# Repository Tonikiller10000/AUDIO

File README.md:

# AUDIO
Some audio related projects(amps, pedals, midi, etc.).

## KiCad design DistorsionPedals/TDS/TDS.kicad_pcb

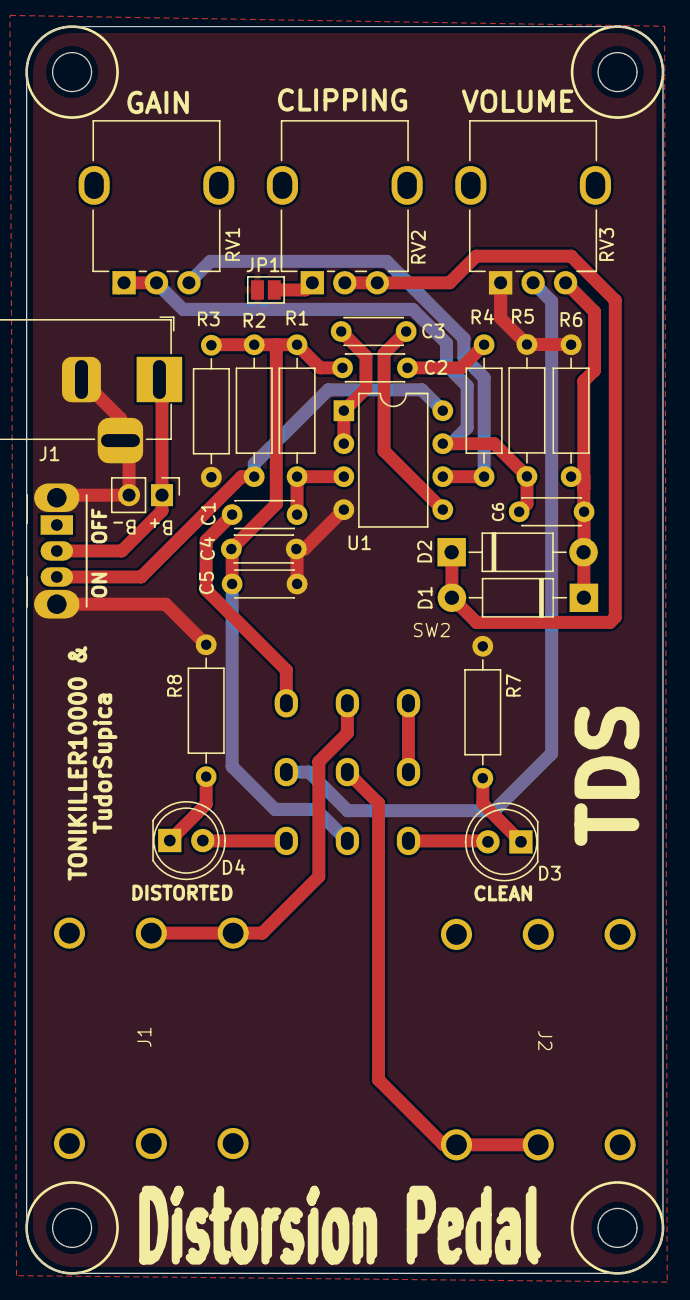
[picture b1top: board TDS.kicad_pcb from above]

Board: 2 copper layers, 49.0 x 96.0 mm, 29 parts (0 on the bottom side), 22 nets.

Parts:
C1, C2, C3, C4, C6: 10uF; C_Disc_D4.3mm_W1.9mm_P5.00mm
C5: 100nF; C_Disc_D4.3mm_W1.9mm_P5.00mm
D1, D2: D; D_DO-41_SOD81_P10.16mm_Horizontal
D3: GREEN; LED_D5.0mm
D4: RED; LED_D5.0mm
J1: Barrel_Jack; BarrelJack_Horizontal
J1#2: Barrel_Jack; PJ-664C
J2: BATT; PinHeader_1x02_P2.54mm_Vertical
J2#2: BATT; PJ-664C
JP1: Jumper_2_Open; SolderJumper-2_P1.3mm_Open_Pad1.0x1.5mm
R1: 100k; R_Axial_DIN0207_L6.3mm_D2.5mm_P10.16mm_Horizontal
R2, R3, R6: 10K; R_Axial_DIN0207_L6.3mm_D2.5mm_P10.16mm_Horizontal
R4, R7, R8: 1K; R_Axial_DIN0207_L6.3mm_D2.5mm_P10.16mm_Horizontal
R5: 3.8K; R_Axial_DIN0207_L6.3mm_D2.5mm_P10.16mm_Horizontal
RV1, RV3: 100K; Potentiometer_Alpha_RD901F-40-00D_Single_Vertical
RV2: 10K; Potentiometer_Alpha_RD901F-40-00D_Single_Vertical
SW1: POW; SW_CuK_OS102011MA1QN1_SPDT_Angled
SW2: FootSwitch
U1: TL072; DIP-8_W7.62mm

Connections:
CLEAN: C1.1, SW2.1 (C)
DISTORTED: RV3.2, SW2.4 (C)
GND: C4.1, C5.1, J1.2, J1.3, J2.2, JP1.2 (B), R3.1, R5.1, R6.1, R7.1, R8.1, RV3.1, U1.4 (V-)
INPUT: J1#2.L, J1#2.R, SW2.2 (B)
unnamed: C2.2, R4.2
unnamed: C6.2, R5.2, RV1.1, RV1.2, U1.7
unnamed: D1.2 (A), D2.1 (K), RV2.2, RV2.3
unnamed: C6.1, D1.1 (K), D2.2 (A), R6.2, RV3.3
unnamed: D3.2 (A), SW2.9 (A)
unnamed: D3.1 (K), R7.2
unnamed: D4.2 (A), SW2.7 (C)
unnamed: D4.1 (K), R8.2
unnamed: JP1.1 (A), RV2.1
unnamed: SW2.3 (A), SW2.6 (A)
unnamed: C1.2, R1.1, U1.3 (+)
unnamed: C3.2, U1.1, U1.2 (-)
unnamed: C3.1, U1.5 (+)
unnamed: R4.1, RV1.3, U1.6 (-)
OUTPUT: J2#2.L, J2#2.R, SW2.5 (B)
POW: J1.1, J2.1, SW1.2 (B)
VCC: R2.2, SW1.3 (A), U1.8 (V+)
VDD: C2.1, C4.2, C5.2, R1.2, R2.1, R3.2, SW2.8 (B)

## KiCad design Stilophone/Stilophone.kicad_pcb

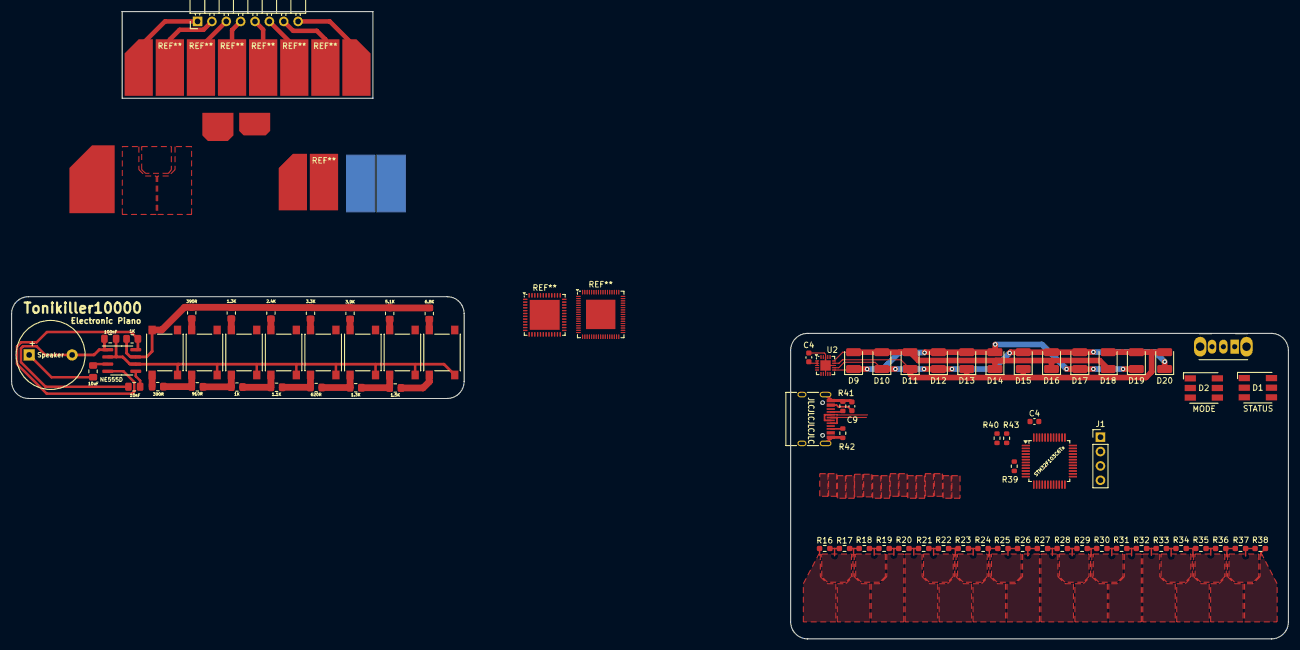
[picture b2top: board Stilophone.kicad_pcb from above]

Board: 2 copper layers, 225.7 x 110.9 mm, 78 parts (0 on the bottom side), 53 nets.

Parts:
C1: 10nF; C_0805_2012Metric_Pad1.18x1.45mm_HandSolder
C2: 100nF; C_0805_2012Metric_Pad1.18x1.45mm_HandSolder
C3: 10uF; C_0805_2012Metric_Pad1.18x1.45mm_HandSolder
C4, C4#2, C9: 10uF; C_0603_1608Metric
D1: STATUS; LED_RGB_5050-6
D2: MODE; LED_RGB_5050-6
D9, D10, D11, D12, D13, D14, D15, D16, D17, D18, D19, D20: D; LED_1210_3225Metric_Pad1.42x2.65mm_HandSolder
J1: STLINK; PinHeader_1x04_P2.54mm_Vertical
J2: USB_C_USB2.0; USB_C_Receptacle_HRO_TYPE-C-31-M-12
LS1: Speaker; Buzzer_12x9.5RM7.6
R1, R6: 1K; R_0805_2012Metric_Pad1.20x1.40mm_HandSolder
R2, R3: 390R; R_0805_2012Metric_Pad1.20x1.40mm_HandSolder
R4: 910R; R_0805_2012Metric_Pad1.20x1.40mm_HandSolder
R5, R12: 1.3K; R_0805_2012Metric_Pad1.20x1.40mm_HandSolder
R7: 2.4K; R_0805_2012Metric_Pad1.20x1.40mm_HandSolder
R8: 1.1K; R_0805_2012Metric_Pad1.20x1.40mm_HandSolder
R9: 3.3K; R_0805_2012Metric_Pad1.20x1.40mm_HandSolder
R10: 620R; R_0805_2012Metric_Pad1.20x1.40mm_HandSolder
R11: 3.9K; R_0805_2012Metric_Pad1.20x1.40mm_HandSolder
R13: 5.1K; R_0805_2012Metric_Pad1.20x1.40mm_HandSolder
R14: 1.5K; R_0805_2012Metric_Pad1.20x1.40mm_HandSolder
R15: 6.8K; R_0805_2012Metric_Pad1.20x1.40mm_HandSolder
R16, R17, R18, R19, R20, R21, R22, R23, R24, R25, R26, R27, R28, R29, R30, R31, R32, R33, R34, R35, R36, R37, R38: R; R_0603_1608Metric_Pad0.98x0.95mm_HandSolder
R39, R40, R43: 10K; R_0603_1608Metric
R41, R42: 5K1; R_0603_1608Metric
SW1: SW_Push; SW_CuK_OS102011MA1QN1_SPDT_Angled
SW1#2, SW2, SW3, SW4, SW5, SW6, SW7, SW8: SW_Push; SW_Push_1P1T_NO_6x6mm_H9.5mm
U1: NE555D; SOIC-8_3.9x4.9mm_P1.27mm
U2: UQFN-20-1EP_3x3mm_P0.4mm_EP1.85x1.85mm
U3: STM32F103C6Tx; LQFP-48_7x7mm_P0.5mm

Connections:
+3.3V: J1.1, R39.2, R40.2, R43.2, U3.1 (VBAT), U3.9 (VDDA), U3.24 (VDD), U3.36 (VDD), U3.48 (VDD)
+5V: C4.1, C4#2.1, U2.1 (VIN), U2.2 (VIN), U2.3 (VCC)
Earth: C1.1, C2.2, LS1.2, U1.1 (GND)
GND: C4.2, C4#2.2, C9.2, J1.4, R16.2, R41.2, R42.2, U2.8 (GND), U2.13 (GND), U2.18 (GND), U2.21 (GND), U3.8 (VSSA), U3.23 (VSS), U3.35 (VSS), U3.47 (VSS)
LED3A: D11.1 (K), D13.1 (K), D15.1 (K), D18.2 (A), D19.2 (A), D20.2 (A), U2.14 (LEDB3)
LED4A: D9.2 (A), D10.2 (A), D11.2 (A), D14.1 (K), D16.1 (K), D18.1 (K), U2.15 (LEDB4)
LEDA1: D9.1 (K), D12.2 (A), D13.2 (A), D14.2 (A), D17.1 (K), D19.1 (K), U2.11 (LEDB1)
LEDA2: D10.1 (K), D12.1 (K), D15.2 (A), D16.2 (A), D17.2 (A), D20.1 (K), U2.12 (LEDB2)
NOTE: R38.1, U3.10 (PA0)
unnamed: C3.2, LS1.1
unnamed: D1.1 (BA), D1.2 (RA), D1.3 (GA), D2.4 (GK), U2.6 (LEDA1)
unnamed: D1.6 (BK), D2.1 (BA), D2.2 (RA), D2.3 (GA), U2.7 (LEDA2)
unnamed: D1.4 (GK), D2.5 (RK), U2.10 (LED4A)
unnamed: D1.5 (RK), D2.6 (BK), U2.9 (LED3A)
unnamed: R2.1, R3.1, R4.2, SW2.1
unnamed: R4.1, R5.1, R6.2, SW3.1
unnamed: R6.1, R7.1, R8.2, SW4.1
unnamed: R10.1, R11.1, R12.2, SW6.1
unnamed: R8.1, R9.1, R10.2, SW5.1
unnamed: R12.1, R13.1, R14.2, SW7.1
unnamed: R14.1, R15.1, SW8.1
unnamed: R16.1, R17.1
unnamed: R17.2, R18.2
unnamed: R18.1, R19.2
unnamed: R19.1, R20.2
unnamed: R20.1, R21.1
unnamed: R21.2, R22.2
unnamed: R22.1, R23.2
unnamed: R23.1, R24.2
unnamed: R24.1, R25.1
unnamed: R25.2, R26.2
unnamed: R26.1, R27.2
unnamed: R27.1, R28.2
unnamed: R28.1, R29.1
unnamed: R29.2, R30.2
unnamed: R30.1, R31.2
unnamed: R31.1, R32.2
unnamed: R32.1, R33.1
unnamed: R33.2, R34.2
unnamed: R34.1, R35.2
unnamed: R35.1, R36.2
unnamed: R36.1, R37.1
unnamed: R37.2, R38.2
unnamed: C1.2, U1.5 (CV)
unnamed: R1.2, R2.2, R3.2, R5.2, R7.2, R9.2, R11.2, R13.2, R15.2, SW1.1, SW1#2.1, U1.7 (DIS)
unnamed: C3.1, U1.3 (Q)
unnamed: C2.1, SW1.2, SW1#2.2, SW2.2, SW3.2, SW4.2, SW5.2, SW6.2, SW7.2, SW8.2, U1.2 (TR), U1.6 (THR)
unnamed: R39.1, U3.7 (NRST)
SCL: R40.1, U2.4 (SCL)
SDA: R43.1, U2.5 (SDA)
SWCLK: J1.3, U3.37 (SYS_JTCK-SWCLK)
SWDIO: J1.2, U3.34 (SYS_JTMS-SWDIO)
VCC: R1.1, U1.4 (R), U1.8 (VCC)

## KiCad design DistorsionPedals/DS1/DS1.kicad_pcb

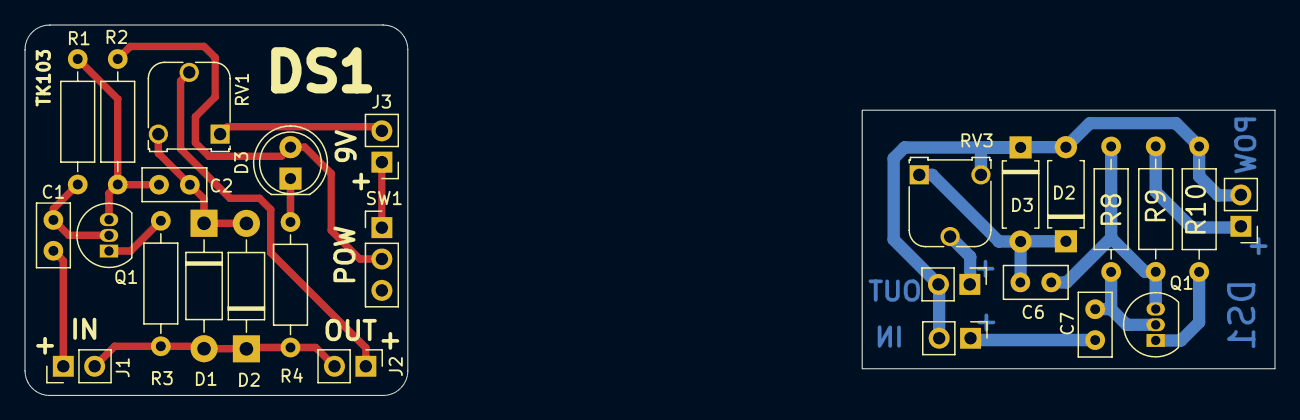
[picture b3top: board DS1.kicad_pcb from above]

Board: 2 copper layers, 101.2 x 30.0 mm, 24 parts (0 on the bottom side), 10 nets.

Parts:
C1, C2, C6, C7: 100nF; C_Disc_D5.0mm_W2.5mm_P2.50mm
D1, D2#2: D; D_DO-41_SOD81_P10.16mm_Horizontal
D2, D3: D; D_A-405_P7.62mm_Horizontal
D3#2: RED; LED_D5.0mm
J1, J2: Conn_01x02; PinHeader_1x02_P2.54mm_Vertical
J3: 9V_BATT; PinHeader_1x02_P2.54mm_Vertical
Q1, Q1#2: 2N3904; TO-92_Inline
R1, R8: 2.2M; R_Axial_DIN0207_L6.3mm_D2.5mm_P10.16mm_Horizontal
R2, R9: 47K; R_Axial_DIN0207_L6.3mm_D2.5mm_P10.16mm_Horizontal
R3, R10: 680R; R_Axial_DIN0207_L6.3mm_D2.5mm_P10.16mm_Horizontal
R4: 10K; R_Axial_DIN0207_L6.3mm_D2.5mm_P10.16mm_Horizontal
RV1, RV3: 100K; Potentiometer_Runtron_RM-065_Vertical
SW1: ENABLE; PinHeader_1x03_P2.54mm_Vertical

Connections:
+9V: D3#2.2 (A), R2.2, R9.2, SW1.2 (B)
GND: D1.2 (A), D2.2 (A), D2#2.1 (K), D3.1 (K), J1.2, J2.2, J3.2, R3.1, R4.1, R10.1, RV1.1, RV3.3
IN: C1.1, C7.1, J1.1
unnamed: C2.2, D1.1 (K), D2#2.2 (A), RV1.3
unnamed: D3#2.1 (K), R4.2
unnamed: J3.1, SW1.1 (C)
unnamed: C1.2, C7.2, Q1.2 (B), Q1#2.2 (B), R1.1, R8.1
unnamed: C2.1, C6.1, Q1.3 (C), Q1#2.3 (C), R1.2, R2.1, R8.2, R9.1
unnamed: Q1.1 (E), Q1#2.1 (E), R3.2, R10.2
OUT: J2.1, RV1.2, RV3.2

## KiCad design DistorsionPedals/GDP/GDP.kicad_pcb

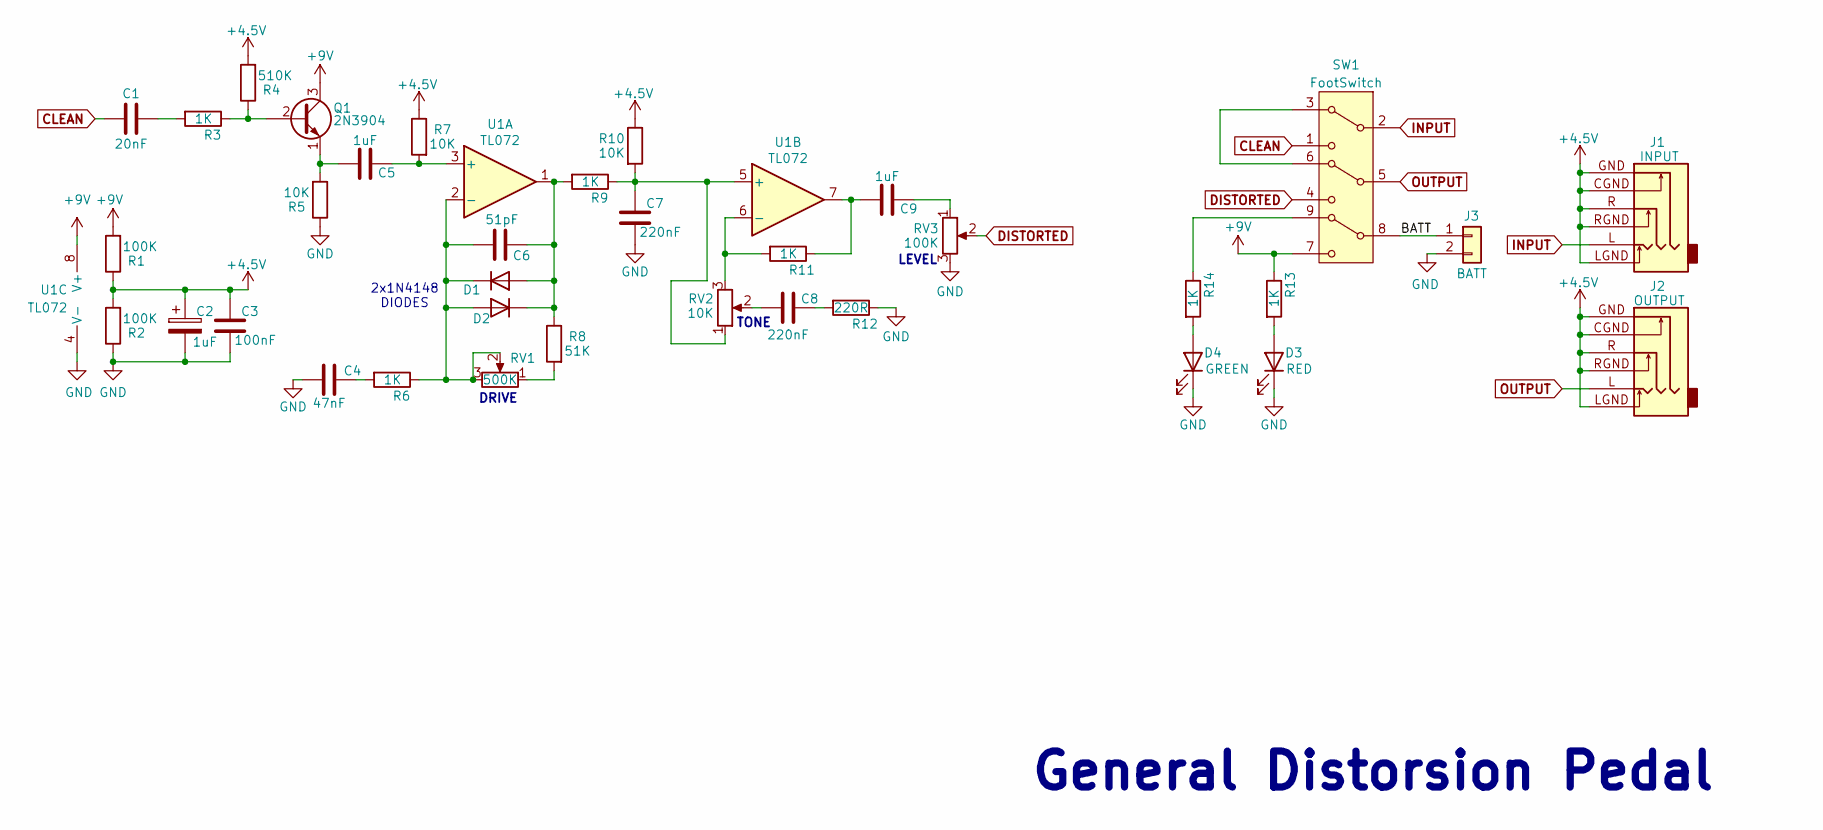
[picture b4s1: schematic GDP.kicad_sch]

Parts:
C1: 20nF; C_Disc_D4.3mm_W1.9mm_P5.00mm
C2: 1uF
C3: 100nF; C_Disc_D4.3mm_W1.9mm_P5.00mm
C4: 47nF; C_Disc_D4.3mm_W1.9mm_P5.00mm
C5, C9: 1uF; C_Disc_D4.3mm_W1.9mm_P5.00mm
C6: 51pF; C_Disc_D4.3mm_W1.9mm_P5.00mm
C7, C8: 220nF; C_Disc_D4.3mm_W1.9mm_P5.00mm
D1, D2: D; D_DO-41_SOD81_P10.16mm_Horizontal
D3: RED; LED_D5.0mm
D4: GREEN; LED_D5.0mm
J1: INPUT
J2: OUTPUT
J3: BATT
Q1: 2N3904; TO-92_Inline
R1, R2: 100K; R_Axial_DIN0207_L6.3mm_D2.5mm_P10.16mm_Horizontal
R3, R6, R9, R11, R13, R14: 1K; R_Axial_DIN0207_L6.3mm_D2.5mm_P10.16mm_Horizontal
R4: 510K; R_Axial_DIN0207_L6.3mm_D2.5mm_P10.16mm_Horizontal
R5, R7, R10: 10K; R_Axial_DIN0207_L6.3mm_D2.5mm_P10.16mm_Horizontal
R8: 51K; R_Axial_DIN0207_L6.3mm_D2.5mm_P10.16mm_Horizontal
R12: 220R; R_Axial_DIN0207_L6.3mm_D2.5mm_P10.16mm_Horizontal
RV1: 500K
RV2: 10K
RV3: 100K
SW1: FootSwitch; Nidec_Copal_CAS-120A
U1: TL072; DIP-8_W7.62mm

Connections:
+4.5V: C2.1, C3.2, J1.CGND, J1.GND, J1.LGND, J1.R, J1.RGND, J2.CGND, J2.GND, J2.LGND, J2.R, J2.RGND, R1.1, R2.2, R4.2, R7.1, R10.1
+9V: Q1.3 (C), R1.2, R13.1, SW1.7 (C), U1.8 (V+)
/BATT: J3.1, SW1.8 (B)
CLEAN: C1.1, SW1.1 (C)
DISTORTED: RV3.2, SW1.4 (C)
GND: C2.2, C3.1, C4.2, C7.1, D3.1 (K), D4.1 (K), J3.2, R2.1, R5.1, R12.1, RV3.3, U1.4 (V-)
INPUT: J1.L, SW1.2 (B)
unnamed: C1.2, R3.2
unnamed: C4.1, R6.2
unnamed: C8.1, R12.2
unnamed: C8.2, RV2.2
unnamed: C9.1, RV3.1
unnamed: C9.2, R11.1, U1.7
unnamed: C6.2, D1.2 (A), D2.1 (K), R8.1, R9.2, U1.1
unnamed: C6.1, D1.1 (K), D2.2 (A), R6.1, RV1.2, RV1.3, U1.2 (-)
unnamed: D3.2 (A), R13.2
unnamed: D4.2 (A), R14.2
unnamed: Q1.2 (B), R3.1, R4.1
unnamed: C5.2, Q1.1 (E), R5.2
unnamed: R8.2, RV1.1
unnamed: R14.1, SW1.9 (A)
unnamed: SW1.3 (A), SW1.6 (A)
unnamed: C5.1, R7.2, U1.3 (+)
unnamed: C7.2, R9.1, R10.2, RV2.1, U1.5 (+)
unnamed: R11.2, RV2.3, U1.6 (-)
OUTPUT: J2.L, SW1.5 (B)

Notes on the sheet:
General Distorsion Pedal
LEVEL
TONE
2x1N4148 DIODES
DRIVE

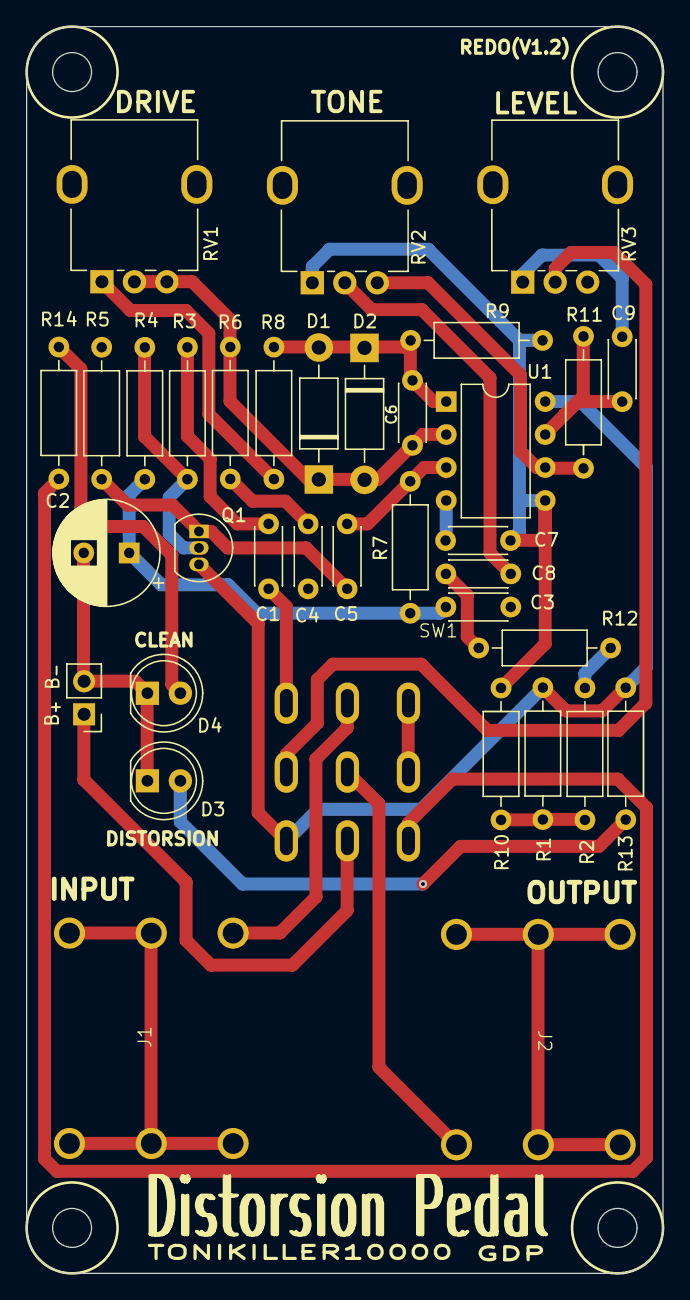
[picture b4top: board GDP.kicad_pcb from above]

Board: 2 copper layers, 49.0 x 96.0 mm, 36 parts (0 on the bottom side), 26 nets.

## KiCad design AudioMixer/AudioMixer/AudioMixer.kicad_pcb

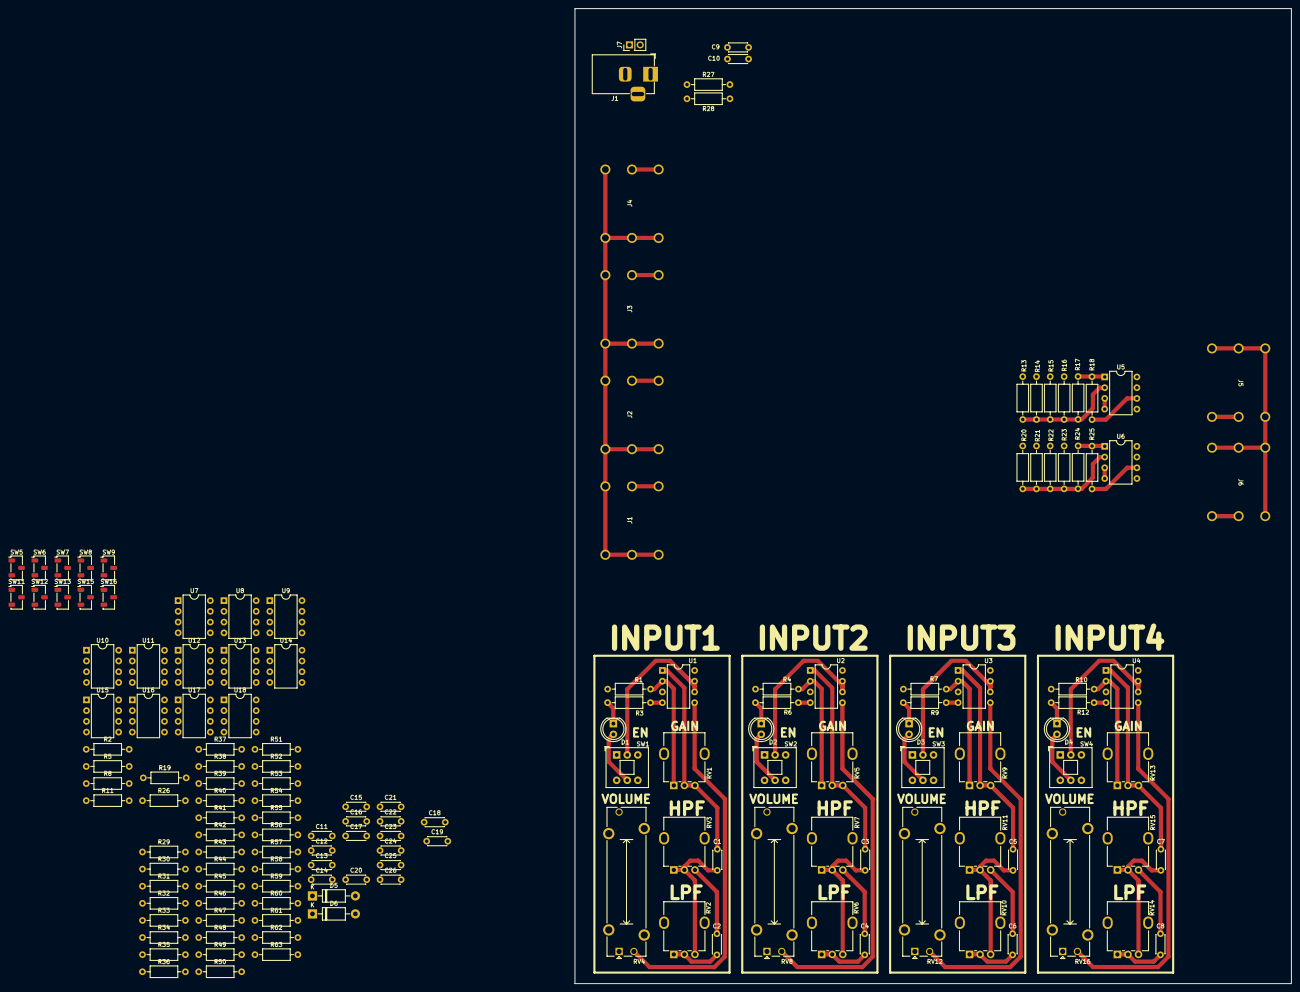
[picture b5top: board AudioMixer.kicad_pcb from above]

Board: 2 copper layers, 169.6 x 230.8 mm, 151 parts (0 on the bottom side), 94 nets.

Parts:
C1, C2, C3, C4, C5, C6, C7, C8, C11, C18, C21, C22, C23, C24, C25, C26: 10uF; C_Disc_D4.3mm_W1.9mm_P5.00mm
C9, C10, C14, C15, C19: 100nF; C_Disc_D4.3mm_W1.9mm_P5.00mm
C12, C13, C16, C17: 10nF; C_Disc_D4.3mm_W1.9mm_P5.00mm
C20: C; C_Disc_D4.3mm_W1.9mm_P5.00mm
D1, D2, D3, D4: RED; LED_D5.0mm
D5, D6: D; D_DO-41_SOD81_P10.16mm_Horizontal
J1, J2, J3, J4: INPUT; PJ-664C
J1#2: Barrel_Jack; BarrelJack_Horizontal
J5, J6: OUTPUT; PJ-664C
J7: PinHeader_1x02_P2.54mm_Vertical
R1, R4, R7, R10, R18, R19, R25, R26, R41, R45, R53, R58, R59, R61, R62: 1K; R_Axial_DIN0207_L6.3mm_D2.5mm_P10.16mm_Horizontal
R2, R3, R5, R6, R8, R9, R11, R12, R30, R31, R34, R37, R38, R39, R40, R42: 10K; R_Axial_DIN0207_L6.3mm_D2.5mm_P10.16mm_Horizontal
R13, R14, R15, R16, R17, R20, R21, R22, R23, R24, R28, R29, R32, R33, R46, R47, R48, R49, R50, R51, R52, R54, R55, R56, R57, R60, R63: 100K; R_Axial_DIN0207_L6.3mm_D2.5mm_P10.16mm_Horizontal
R27: 47K; R_Axial_DIN0207_L6.3mm_D2.5mm_P10.16mm_Horizontal
R35: 33K; R_Axial_DIN0207_L6.3mm_D2.5mm_P10.16mm_Horizontal
R36: 68K; R_Axial_DIN0207_L6.3mm_D2.5mm_P10.16mm_Horizontal
R43, R44: R; R_Axial_DIN0207_L6.3mm_D2.5mm_P10.16mm_Horizontal
RV1, RV2, RV3, RV5, RV6, RV7, RV9, RV10, RV11, RV13, RV14, RV15: 100K; Potentiometer_Alpha_RD901F-40-00D_Single_Vertical
RV4, RV8, RV12, RV16: 100K; Potentiometer_Bourns_PTA2043_Single_Slide
SW1, SW2, SW3, SW4: EN; SW_Push_2P2T_Toggle_CK_PVA2xxH3xxxxxxV2
SW5, SW6: EN; Nidec_Copal_CAS-120A
SW7: POW; Nidec_Copal_CAS-120A
SW8, SW9, SW11, SW12, SW13, SW15, SW16: CH1; Nidec_Copal_CAS-120A
U1, U2, U3, U4, U5, U6, U7, U8, U9, U10, U11, U12, U13, U14, U16, U17, U18: TL072; DIP-8_W7.62mm
U15: NE555P; DIP-8_W7.62mm

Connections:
3V: R32.1, R33.1
+4.5V: U9.6 (-), U10.5 (+)
/INPUT1: J1.L, J1.R, R2.2, U1.3 (+)
/INPUT2: J2.L, J2.R, R5.2, U2.3 (+)
/INPUT3: J3.L, J3.R, R8.2, U3.3 (+)
/INPUT4: J4.L, J4.R, R11.2, U4.3 (+)
CH1_to_OUT1: R13.2, R20.2, SW12.1 (C)
CH2_to_OUT1: R14.2, R21.2
CH3_to_OUT1: R15.2, R22.2
CH4_to_OUT1: R16.2, R23.2
GND: C2.2, C4.2, C6.2, C8.2, C11.1, C15.1, C16.1, C17.1, C18.1, C19.1, C20.1, C22.2, C24.2, C26.2, R1.2, R3.1, R4.2, R6.1, R7.2, R9.1, R10.2, R12.1, R34.1, R35.2, R41.1, R42.1, R45.2, R53.2, R62.2, RV3.3, RV4.1, RV7.3, RV8.1, RV11.3, RV12.1, RV15.3, RV16.1, U1.4 (V-), U2.4 (V-), U3.4 (V-), U4.4 (V-), U5.3 (+), U5.4 (V-), U5.5 (+), U6.3 (+), U6.4 (V-), U6.5 (+), U7.5 (+), U8.5 (+), U11.4 (V-), U12.5 (+), U15.1 (GND), U16.5 (+), U17.5 (+), U18.5 (+)
unnamed: C1.1, RV2.3, RV3.1, RV3.2
unnamed: C1.2, RV1.2, RV1.3, U1.1
unnamed: C2.1, RV2.1, RV2.2, RV4.3
unnamed: C3.1, RV6.3, RV7.1, RV7.2
unnamed: C3.2, RV5.2, RV5.3, U2.1
unnamed: C4.1, RV6.1, RV6.2, RV8.3
unnamed: C5.1, RV10.3, RV11.1, RV11.2
unnamed: C5.2, RV9.2, RV9.3, U3.1
unnamed: C6.1, RV10.1, RV10.2, RV12.3
unnamed: C7.1, RV14.3, RV15.1, RV15.2
unnamed: C7.2, RV13.2, RV13.3, U4.1
unnamed: C8.1, RV14.1, RV14.2, RV16.3
unnamed: C9.1, R27.2, U10.7
unnamed: C10.1, R29.1, U12.7
unnamed: C12.1, C13.2, C16.2, C17.2
unnamed: C12.2, R37.2, R39.1, U14.7
unnamed: C21.2, C23.2, C25.2, R59.1
unnamed: D1.2 (A), SW1.5 (B)
unnamed: D1.1 (K), R3.2
unnamed: D2.2 (A), SW2.5 (B)
unnamed: D2.1 (K), R6.2
unnamed: D3.2 (A), SW3.5 (B)
unnamed: D3.1 (K), R9.2
unnamed: D4.2 (A), SW4.5 (B)
unnamed: D4.1 (K), R12.2
unnamed: D5.2 (A), D6.1 (K)
unnamed: D5.1 (K), D6.2 (A), SW15.3 (A), SW16.3 (A)
unnamed: R17.1, R18.2, U5.1
unnamed: R24.1, R25.2, U6.1, U7.7
unnamed: R28.1, U9.7
unnamed: R30.2, R31.2, U11.7
unnamed: R36.1, U13.7
unnamed: R37.1, R38.2
unnamed: R46.2, U16.1
unnamed: R56.2, U11.1
unnamed: R57.1, R58.2, U17.7
unnamed: R60.1, R61.2, U18.7
unnamed: R63.2, U17.1
unnamed: U6.7, U8.7
unnamed: SW1.2 (B), U1.6 (-), U1.7
unnamed: SW2.2 (B), U2.6 (-), U2.7
unnamed: SW3.2 (B), U3.6 (-), U3.7
unnamed: SW4.2 (B), U4.6 (-), U4.7
unnamed: R19.1, SW5.2 (B)
unnamed: R26.1, SW6.2 (B)
unnamed: SW8.2 (B), SW9.2 (B), SW11.2 (B), SW12.2 (B), SW13.2 (B)
unnamed: SW15.1 (C), SW16.1 (C)
unnamed: R1.1, RV1.1, U1.2 (-)
unnamed: RV4.2, U1.5 (+)
unnamed: R4.1, RV5.1, U2.2 (-)
unnamed: RV8.2, U2.5 (+)
unnamed: R7.1, RV9.1, U3.2 (-)
unnamed: RV12.2, U3.5 (+)
unnamed: R10.1, RV13.1, U4.2 (-)
unnamed: RV16.2, U4.5 (+)
unnamed: R13.1, R14.1, R15.1, R16.1, R17.2, U5.2 (-)
unnamed: R18.1, U5.6 (-)
unnamed: R20.1, R21.1, R22.1, R23.1, R24.2, U6.2 (-)
unnamed: R25.1, U6.6 (-)
unnamed: R27.1, R28.2, U9.5 (+)
unnamed: C9.2, U10.6 (-)
unnamed: C24.1, U11.3 (+)
unnamed: R53.1, U11.2 (-)
unnamed: R31.1, R34.2, U11.5 (+)
unnamed: C11.2, U11.6 (-)
unnamed: C10.2, R29.2, R30.1, U12.6 (-)
unnamed: C14.2, C15.2, U13.5 (+)
unnamed: R35.1, R36.2, U13.6 (-)
unnamed: R39.2, R41.2, U14.5 (+)
unnamed: C13.1, R38.1, U14.6 (-)
unnamed: R43.1, R44.2, U15.7 (DIS)
unnamed: C20.2, R44.1, U15.2 (TR), U15.6 (THR)
unnamed: C22.1, U16.3 (+)
unnamed: R45.1, U16.2 (-)
unnamed: R58.1, U16.6 (-)
unnamed: C26.1, U17.3 (+)
unnamed: R62.1, U17.2 (-)
unnamed: R57.2, U17.6 (-)
unnamed: R60.2, U18.6 (-)
OUTPUT1: J5.L, J5.R, SW5.3 (A), SW6.3 (A)
OUTPUT2: J6.L, J6.R
VCC: C18.2, C19.2, R40.1, R42.2, R43.2, U15.4 (R), U15.8 (VCC)
VDD: J1.CGND, J1.GND, J1.LGND, J1.RGND, J2.CGND, J2.GND, J2.LGND, J2.RGND, J3.CGND, J3.GND, J3.LGND, J3.RGND, J4.CGND, J4.GND, J4.LGND, J4.RGND, J5.CGND, J5.GND, J5.LGND, J5.RGND, J6.CGND, J6.GND, J6.LGND, J6.RGND, R2.1, R5.1, R8.1, R11.1, R40.2, SW1.6 (C), SW2.4 (A), SW3.4 (A), SW4.4 (A), SW7.3 (A), U1.8 (V+), U2.8 (V+), U3.8 (V+), U4.8 (V+), U5.8 (V+), U6.8 (V+), U11.8 (V+)

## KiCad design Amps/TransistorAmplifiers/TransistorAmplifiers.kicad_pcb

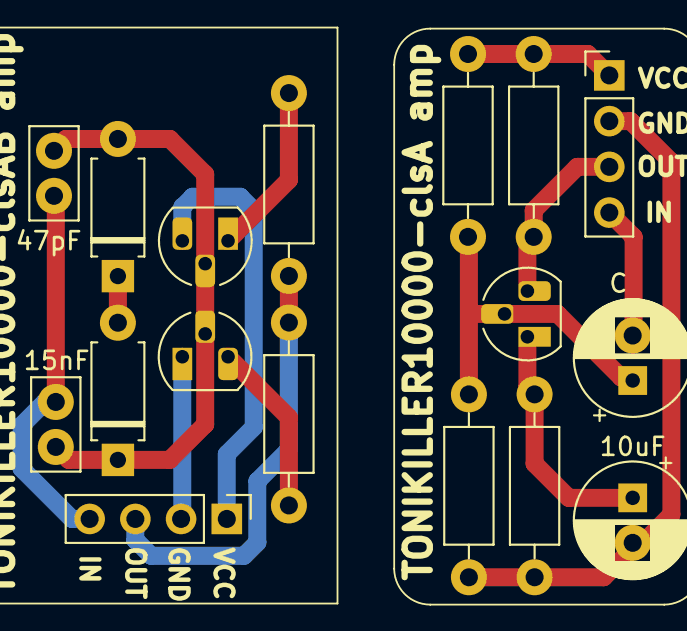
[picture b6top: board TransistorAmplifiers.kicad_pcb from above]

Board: 2 copper layers, 15 parts (0 on the bottom side), 2 nets.

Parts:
C9: 47pF; C_Disc_D5.0mm_W2.5mm_P2.50mm
C10: 15nF; C_Disc_D5.0mm_W2.5mm_P2.50mm
C23: 10uF; CP_Radial_D6.3mm_P2.50mm
C29: C; CP_Radial_D6.3mm_P2.50mm
D56, D57: D; D_A-405_P7.62mm_Horizontal
Q180, Q195: SS8050; TO-92_HandSolder
Q196: Ss8550; TO-92_HandSolder
R190, R221: 4.7K; R_Axial_DIN0207_L6.3mm_D2.5mm_P10.16mm_Horizontal
R191, R222: 1K; R_Axial_DIN0207_L6.3mm_D2.5mm_P10.16mm_Horizontal
R202, R203: R; R_Axial_DIN0207_L6.3mm_D2.5mm_P10.16mm_Horizontal

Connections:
GND: Q196.1 (E), R191.1, R222.1
OUT: Q180.3 (C), R190.1, R202.1, R203.2

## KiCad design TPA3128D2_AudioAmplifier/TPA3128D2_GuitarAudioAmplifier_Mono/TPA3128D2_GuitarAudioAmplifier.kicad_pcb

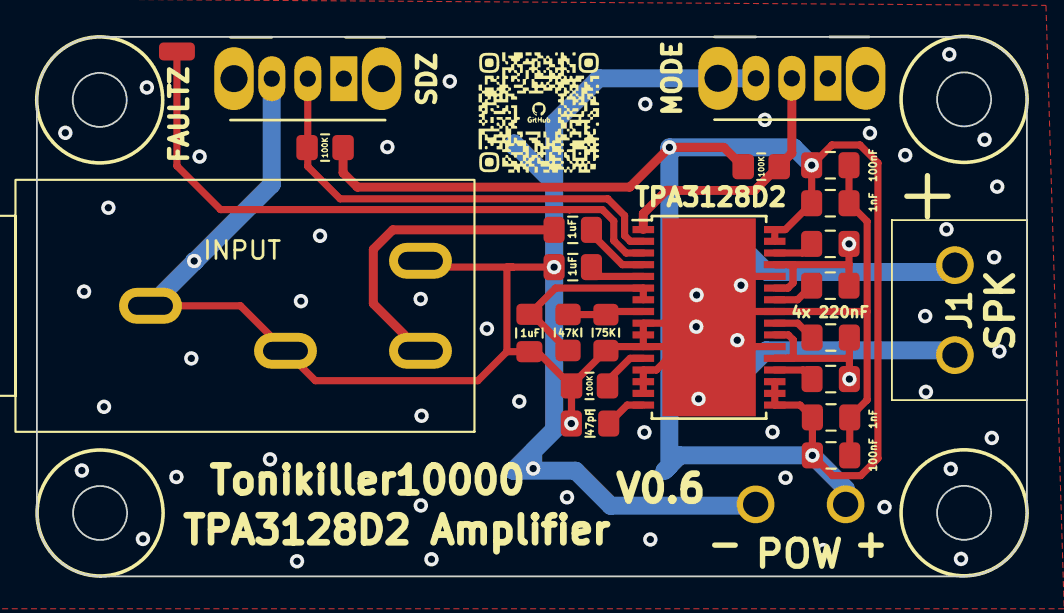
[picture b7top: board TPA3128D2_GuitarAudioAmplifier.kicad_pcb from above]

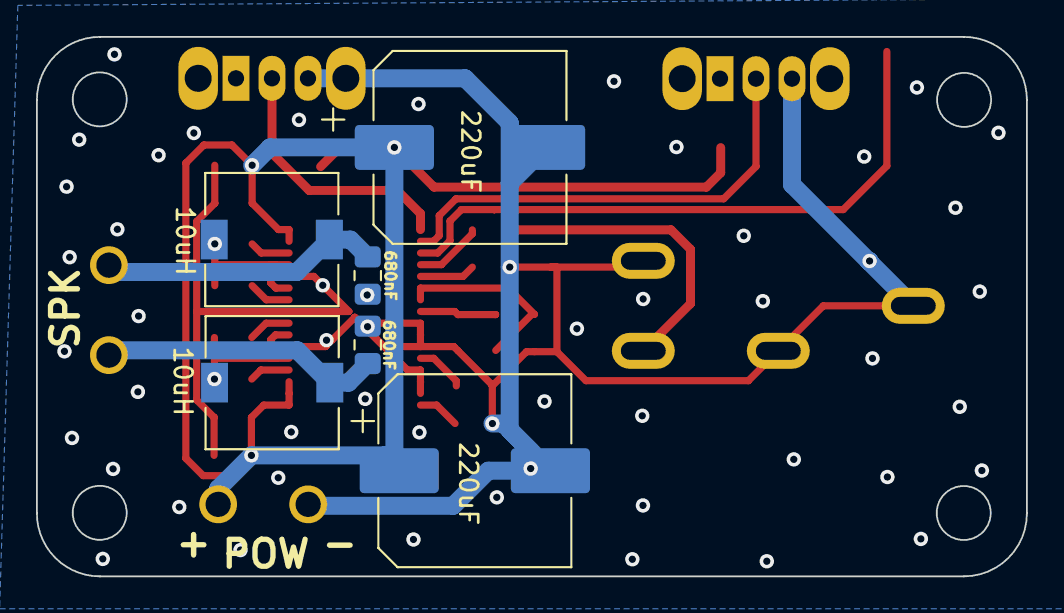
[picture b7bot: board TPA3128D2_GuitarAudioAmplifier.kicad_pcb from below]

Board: 2 copper layers, 55.0 x 30.0 mm, 29 parts (7 on the bottom side), 19 nets.

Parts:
C1, C2: 1nF; C_0805_2012Metric_Pad1.18x1.45mm_HandSolder
C3, C4: 100nF; C_0805_2012Metric_Pad1.18x1.45mm_HandSolder
C5, C7, C8: 1uF; C_0805_2012Metric_Pad1.18x1.45mm_HandSolder
C6, C9: 220uF; CP_Elec_10x10.5
C10: 47pF; C_0805_2012Metric_Pad1.18x1.45mm_HandSolder
C11, C12, C13, C14: 220nF; C_0805_2012Metric_Pad1.18x1.45mm_HandSolder
C15, C16: 680nF; C_0805_2012Metric_Pad1.18x1.45mm_HandSolder
J1, J1#2: SPEAKER; KF3012P
J2: INPUT; Jack_6.35mm_Neutrik_NRJ4HH-1_Horizontal
L1, L2: 10uH; L_7.3x7.3_H4.5
R1: 47K; R_0805_2012Metric_Pad1.20x1.40mm_HandSolder
R2: 75K; R_0805_2012Metric_Pad1.20x1.40mm_HandSolder
R3, R4, R5: 100K; R_0805_2012Metric_Pad1.20x1.40mm_HandSolder
SW1, SW1#2: SW_SPDT; SW_CuK_OS102011MA1QN1_SPDT_Angled
U1: TPA3128D2; HTSSOP-32-1EP_6.1x11mm_P0.65mm_EP5.2x11mm_Mask4.11x4.36mm

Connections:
GND: C1.1, C2.1, C3.1, C4.1, C5.2, C6.2, C8.2, C9.2, C10.1, C15.1, C16.1, J1#2.2, J2.G, J2.R, J2.T, R2.2, R3.2, SW1.3 (C), SW1#2.3 (C), U1.9 (GND), U1.10 (LINP), U1.11 (LINN), U1.13 (AM2), U1.14 (AM1), U1.15 (AM0), U1.22 (GND), U1.25 (GND), U1.28 (GND), U1.33
MODE: R5.1, SW1.2 (B), U1.1 (MODSEL)
MUTE: R3.1, U1.12 (MUTE)
unnamed: C7.2, J2.S
unnamed: C14.1, U1.20 (BSNL)
unnamed: C12.1, U1.26 (BSNR)
unnamed: C13.1, U1.24 (BSPL)
unnamed: C11.1, U1.30 (BSPR)
unnamed: R1.2, R2.1, U1.8 (GAIN/SLV)
unnamed: C5.1, R1.1, U1.6 (PLIMIT), U1.7 (GVDD)
unnamed: C13.2, C14.2, L2.1, U1.21 (OUTNL), U1.23 (OUTPL)
unnamed: C11.2, C12.2, L1.1, U1.27 (OUTNR), U1.29 (OUTPR)
unnamed: C8.1, U1.5 (RINN)
unnamed: C7.1, U1.4 (RINP)
SDZ: R4.1, SW1#2.2 (B), U1.2 (SDZ)
SPK+: C15.2, J1.1, L1.2
SPK-: C16.2, J1.2, L2.2
SYNC: C10.2, U1.16 (SYNC)
VCC: C1.2, C2.2, C3.2, C4.2, C6.1, C9.1, J1#2.1, R4.2, R5.2, U1.17 (AVCC), U1.18 (PVCC), U1.19 (PVCC), U1.31 (PVCC), U1.32 (PVCC)
